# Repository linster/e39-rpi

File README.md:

# e39-rpi
BMW e39 IBUS Raspberry Pi App

Ths program listens to the steering wheel Previous & Next track inputs, and routes those to a paired Bluetooth phone to change the track in Google Play Music. 

Where there has been previous research and work done to interface with the BMW IBus (a LIN bus), I am the first to do it with Kotlin using co-routines, flows, and channels. 

More details are available about the project at https://e39.dev

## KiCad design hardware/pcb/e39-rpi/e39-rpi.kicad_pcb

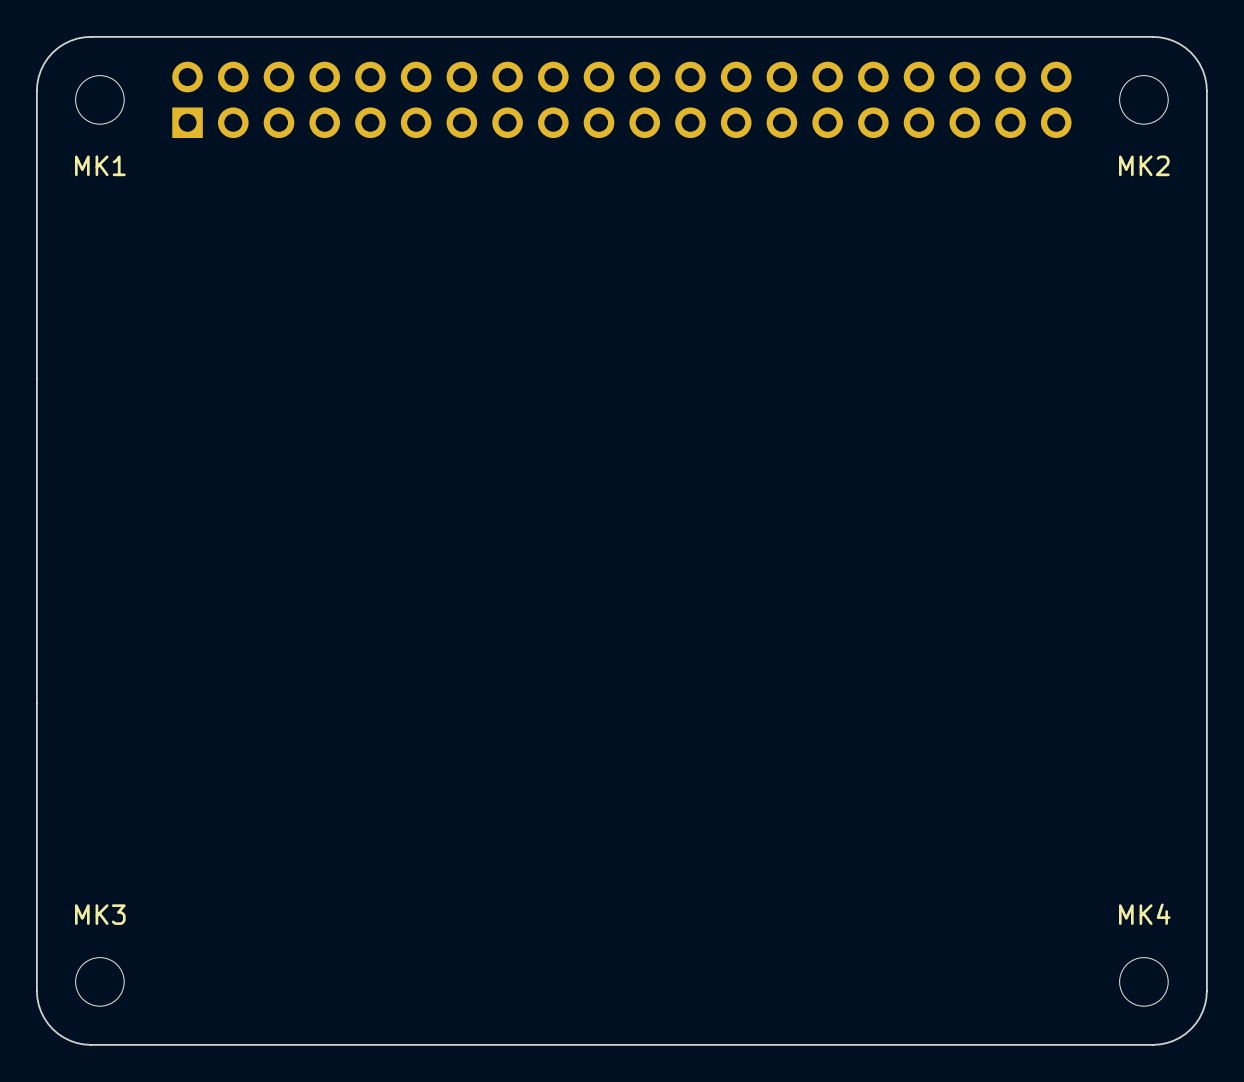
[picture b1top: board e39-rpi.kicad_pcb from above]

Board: 2 copper layers, 65.0 x 56.0 mm, 5 parts (1 on the bottom side), 3 nets, no tracks yet.

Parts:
MK1, MK2, MK3, MK4: M2.5; MountingHole_2.7mm_M2.5
P1: Conn_02x20_Odd_Even; PinSocket_2x20_P2.54mm_Vertical

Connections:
+3V3: P1.1, P1.17
+5V: P1.2, P1.4
GND: P1.6, P1.9, P1.14, P1.20, P1.25, P1.30, P1.34, P1.39

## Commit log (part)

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2021-12-04 FFS
    "Kotlin doesn’t currently support sharing a source set for these combinations:
    Several JVM targets
    JVM + Android targets
    "
    This is exactly what I want to do in the common module with source-sets...
2021-12-05 Switch image builder to 64 bit Raspbian Lite
2021-12-30 Remove bintray
2021-12-31 Add version config to about screen
2021-12-31 test
2022-01-01 Ugly hack to fix IbusInputEvent writer
2022-01-01 Add nav knob parser
2022-01-01 Fix decorations for pi
2022-01-02 Rest of setup
2022-01-04 We can plot points
2022-01-20 We can plot routes and lines.
2022-02-26 Add VGA timings. Start new service group work
2022-03-01 Config profiles working
2022-03-03 Add default map center picker
2022-03-03 Add platform service group settings to HMI
2022-03-03 Show/Hide debug menu on Loading Window
2022-03-07 WIP Themes across all UI
2022-03-08 Themes mostly work, but persistence on app boot doesn't work
2022-03-08 Fixed theme pref persistence
2022-08-06 Start smooth scroll
2022-08-06 WIP POI Editor.
    Added Grid View. Added Image Buttons.
2022-08-06 Composable function references not being allowed shows up in subtle ways.
2022-08-07 POIS work.
2022-08-09 Update version. Add brightness comp
2022-08-13 Guidance setup almost working
2022-08-13 Guidance UI flow works.
2022-08-13 Hook up guidance to UI
2022-08-21 Cleanup MapScreen event bus, state transitions.
    Fix minor bugs in guidance session.
    Start on GuidanceSession debug window.
2022-08-25 Rename some package directives. Add SqlDelight to the project.
2023-01-14 latest
2023-05-19 Pico Comms WIP
2023-05-20 Pico Comms log window seems to work for synthetic IbusInputEvents.
    Sunroof Opener doesn't seem to work at all?
2023-06-17 Update all the kotlin versions.
2023-06-17 Outgoing PiToPicoMessages seem to work.
2023-06-17 I think we can simulate PicoToPi messages now.
2023-07-09 Start ScreenDoc
2023-07-20 Add more screen docs
2023-08-06 Repeatable annotations don't work as expected in Kotlin
2023-12-10 Updates to make serial work again. Not really sure what was going on here, but it runs.
2023-12-10 Cleanup AllowsGoBack
2024-01-14 wip tinkering on screendoc
2024-01-16 Baud Rate setup via config file for different bus topologies.
2024-01-29 Update protobufs
2024-02-02 More debug tools for pico interop
2024-02-23 ConfigPush ui
2024-02-25 Add config option for fw hash
2024-02-25 Remove commented out video things, add sound config from VGA_Zero
2024-02-25 Update build script
2024-02-25 Before trying to mount boot cleanly
2024-02-25 We can pre-populate /boot with vga timings and wifi config now
2024-02-26 Slight cleanup
2024-02-26 Before upgrade to bookworm
2024-03-03 Upgrade to bookworm (gitignore)
2024-03-03 Upgrade to bookworm
2024-03-11 Once the e39firstboot service actually runs, it can set up the device well-enough to boot jwm
2024-03-12 Minor about screen tweaks
2024-03-12 turn up the volume yo
2024-03-12 run the platform after accepting device configuration so that the user isn't stuck after pairing bt
2024-03-12 Clean up bt pairing deadlock
2024-03-13 This is all kinda working... kinda
2024-03-13 Seems to be okay
2024-05-25 Add more themes
2024-05-25 Revolution Orange works
2024-05-26 Add Goose Green
2024-06-19 Add now playing menu
2024-08-04 Now playing screen works. Rewrote a lot of the janky dbus connector /dbus reconnector logic. The BlueeoothEventDispatcher seems to break input everywhere somehow. Not sure what's going on.
    I finally did split up that gigantic bluetooth service from four years ago.
2024-08-18 Failed experiment with checkbox flow, now playing info sources.
2024-08-18 Update protobufs with shutdown message
2024-08-18 Add shutdown parser
2024-08-24 Add screen power writer log statement
2024-11-28 Fuckit let's write a Matrix client. Gotta chat with da boyz on the road.
2024-11-28 Moar chat UI
2024-11-28 WIP we broke it. Damn classpath conflict on kotlin update. Need to update Compose to latest, which needs compiler plugin updates.
    https://www.jetbrains.com/help/kotlin-multiplatform-dev/compose-compiler.html#migrating-a-compose-multiplatform-project
2024-11-29 last kick at the cat before changing project structure for new kotlin multiplatform shennaniganry
2024-12-02 Move main to desktopMain
2024-12-02 WIP moving to new gradle structure so that Kotlin 2.1 is happy, so I can use trixnity because classpath conflict nonsense.
2024-12-03 Bring over root settings.gradle.kts contents
2024-12-03 Move root src to composeApp/src
2024-12-03 keep cleaning main plugins
2024-12-03 Can do a gradle sync, but still have syntax errors in the build scripts.
2025-01-02 Turns out the composeApp gradle build file was in the wrong dir (was under src/)
2025-01-02 getting warmer
2025-01-02 split apart PlatformService annotations, update usages.
2025-01-02 Cleanup broken imports from bad refactor
2025-01-02 Re-add missing compiler opt-ins
2025-01-02 Clear some compilation errors. Looks like we're stuck on not finding DaggerApplicationComponent.
2025-01-02 We can run KAPT now for dagger2, but get an incompatibility for Kotlin 2.0. Time to update dagger.
2025-01-02 We can compile and run, but now we can't find the resources in commonMain
2025-01-03 Plugging away at the matrix chat app
2025-01-03 Add some login graphics
2025-01-03 Room List works
2025-01-03 Room info screen seems to work
2025-01-03 We can load a room into the chat window screen
2025-01-03 fix storage
2025-01-03 gitignore
2025-01-04 Putter on the room uploads list, hide non-essential features
2025-01-27 Just about have the matrix chat hooked up
2025-01-28 Almost have the UI working with updates
2025-01-28 UI tweaks
2025-01-30 move the flow logic away
2025-01-30 Janky AF but it works
2025-01-30 Chat MVP works
2025-02-01 Pictures in the chat work!
2025-02-01 On Screen Keyboard now responds to real keyboard events
2025-09-16 Putter on the calendar
2025-09-16 Make the port re-opening a little more resilient, but really a `killall java` in piDeploy helps the most.
2025-09-16 Print stacktraces to stdout
2025-09-16 Cleanup one column for brevity
2025-09-16 Minor fixes
2025-09-16 Update gitignore
2025-09-16 Spruce up scripts after they broke when the project went to MPP
2025-09-16 WIP Make chat work on the rpi. There's a race condition where larger rooms won't load.
2025-09-16 Redact
2025-09-16 Fix the themes to be presentable
2025-09-16 Redact server Room List works
2025-09-16 Setup remote debugging
2025-09-16 Fix the chat on the pi
2025-09-16 Fix race condition on Overlay knob listener
2025-09-16 Redact Room List works
2025-10-22 Polish up the month view
2025-10-31 woohoo! Knob listeners now work for when menu contents aren't totally known up front. This is actually much nicer than how I had made the other menus :)
2025-11-11 The buttons on the month view work now.
2025-11-16 Dynamic knob listener works now after clicks
2025-11-16 Cleanup some comments
2025-11-17 Navigating between calendar screens work. Clean up some imports IntelliJ screwed up.
2025-11-17 Neat bug
2025-11-28 Hot and fresh nonsense updates.
2025-11-28 Quick and dirty one week view. Need to resolve a JRE version problem.
2025-11-30 NorthButtonRow
2025-12-07 Background for week view
2025-12-07 Add localLib for daily-agenda-view
2025-12-07 Broke it good
2025-12-12 early morning plast
2025-12-12 Bit of a grid goin on
2025-12-13 We can add and remove days at runtime
2025-12-14 We can place data on day 0
2025-12-17 Add some subdivisions
2025-12-17 Recurse to split events to multiday
2025-12-17 Calculate if event is visible on calendar
2025-12-19 Subtract yo
2025-12-20 idk if this'll work but I was in teh zone writing it
2025-12-20 Subdivisions break constaint layout
2025-12-20 Invisible structural nonsense
2025-12-21 Overlaps appear to work
2025-12-21 Agenda Screen scrolls to the future. Knob seems to work.
2025-12-21 Scrolling back in time works
2025-12-22 edit screen
2025-12-22 Date picker works
2025-12-22 Layout for event editor is done, but it doesn't do anything
2025-12-23 towards wiring up the edit window
2025-12-26 Time picker works
2025-12-26 Scrolling left right works
2025-12-26 Scrolling with scrollbars kinda sucks
2026-01-19 Powermate works.
2026-01-19 Sensitivity training
2026-02-10 Fixup the overlay knob
2026-03-18 Calendar event edit screen has the working way to do dynamic knob listener that still works after the modal goes away!
2026-03-19 Cleanup all the other uses of the dynamic knob listener.
2026-03-21 Start cleaning up the map screen. Finish a mission from 2022.
2026-03-21 Maps kinda work again, but the OSM tile server hates us.
2026-03-22 Add powermate config screen
2026-03-22 Random junk
2026-03-22 WIP griffin
2026-03-22 Griffin powermate can be less sensitive on just the map
2026-03-28 Docker is still mostly a mystery
2026-03-28 wizardry. I now have the dbus files I care about.
2026-03-28 Update depdendencies for the first time in a few years lol. Freeze dbus-java generator script to 5.2.0 because their master branch broke the code gen.
2026-03-28 Start on the setHostname screen, but realized the generator didn't generate all the things.
2026-03-28 tin-bash the generator to not be so fussy
2026-03-28 Add the missing generated code. Hope it works!
2026-03-29 Hostname set screen works!
2026-03-29 Clean up the hostname screen
2026-03-29 Make dbus stop shouting at us
2026-03-29 Hook up the activate connection screen
2026-03-29 Start working on the modal that will show the "Connecting..." load state while the active connection window is connecting.
2026-03-29 Modal dialog looks nice
2026-03-29 Activating Connection Dialog has a throbber now :)
2026-04-01 that dummy screen looks handsome
2026-04-02 Smooth scroll almost works!
2026-04-02 Smooth scroll works!
2026-04-02 Clean up the smooth scroll file.
2026-04-02 Fix a longstanding UX issue with PairableDeviceChooser updating so rapidly that it's hard to scroll to the right page to then select a thing.
2026-04-02 Add it to the current device chooser too. Cleanup some code duplication.
2026-04-04 Many steps to disambiguate names. I skipped the ones that need udev.
2026-04-04 WIP devices use cases
2026-04-04 Couple more sub-use-cases work.
2026-04-04 Another working sub-use-case
2026-04-05 molecule still makes no sense
2026-04-05 Moar
2026-04-06 Wifi ssid list works but doesn't update.
2026-04-06 Fixup the infinite recomposition
2026-04-11 Moar filtering
2026-04-12 BT Filtering soup
2026-04-12 Move some files around into different packages
2026-04-12 Add missing UC
2026-04-12 Activate connection screen is pretty happy
2026-04-12 Fix a bug on bt. Add sorting for devices.
2026-04-13 Note for merge
2026-04-13 Add mode
2026-04-14 Add wifi security flags to UI
2026-04-17 Non-wifi connections can be seen as active with a reload of the screen. Crashes when a connection becomes deactivated. (should reload the list to fix -- update the GetAllActiveConnectionsUseCase). Al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
2026-04-17 Wireless access points can now be marked as active.
2026-04-19 Fixup dropping other connections for device when one is active
2026-04-19 We can now live-update the connected connections when nmtui changes them on the side, without a page reload.
2026-04-19 We can now disconnect from connections
2026-04-22 We can connect to networks now! (Just regular ones)
2026-04-26 Move the calendar into an apps package
2026-04-27 Start the PDF viewer
2026-05-01 Work on the SmoothScroll Grid. Will be used for PDF pages, files, and home screen.
2026-05-01 Smooth grid scroll almost done!
2026-05-01 Grid smooth scroll works
2026-05-02 Wip sidebar
2026-05-02 Page selector works. Time to add zoom.
2026-05-02 Working towards a zoom slider
2026-05-02 Page selector works
2026-05-06 Wire up page selector requests and results
2026-05-07 Menu for pdf viewer wip
2026-05-07 Add a few more buttons to the pdf viewer toolbar
2026-05-08 Add more parts to the pdf viewer
2026-05-08 Zoom works. Now need scroll bars.
2026-05-09 Vertical scrollbar works. Horizontal one is tied to the vertical state. Woops!
2026-05-09 Horizontal scroll works
2026-05-09 Make Horizontal scrollbar visible when zoomed in
2026-05-10 Fixed the page selector screen
2026-05-10 Cleanup dead code.
2026-05-12 Search wroks like just once
2026-05-12 Switch test PDFs
2026-05-13 Search explorer pane works!
2026-05-13 Cleanup file structure for pdf reader
2026-05-14 Start Video player screen
2026-05-15 Video playback works
2026-05-15 Finished up the video player screen
